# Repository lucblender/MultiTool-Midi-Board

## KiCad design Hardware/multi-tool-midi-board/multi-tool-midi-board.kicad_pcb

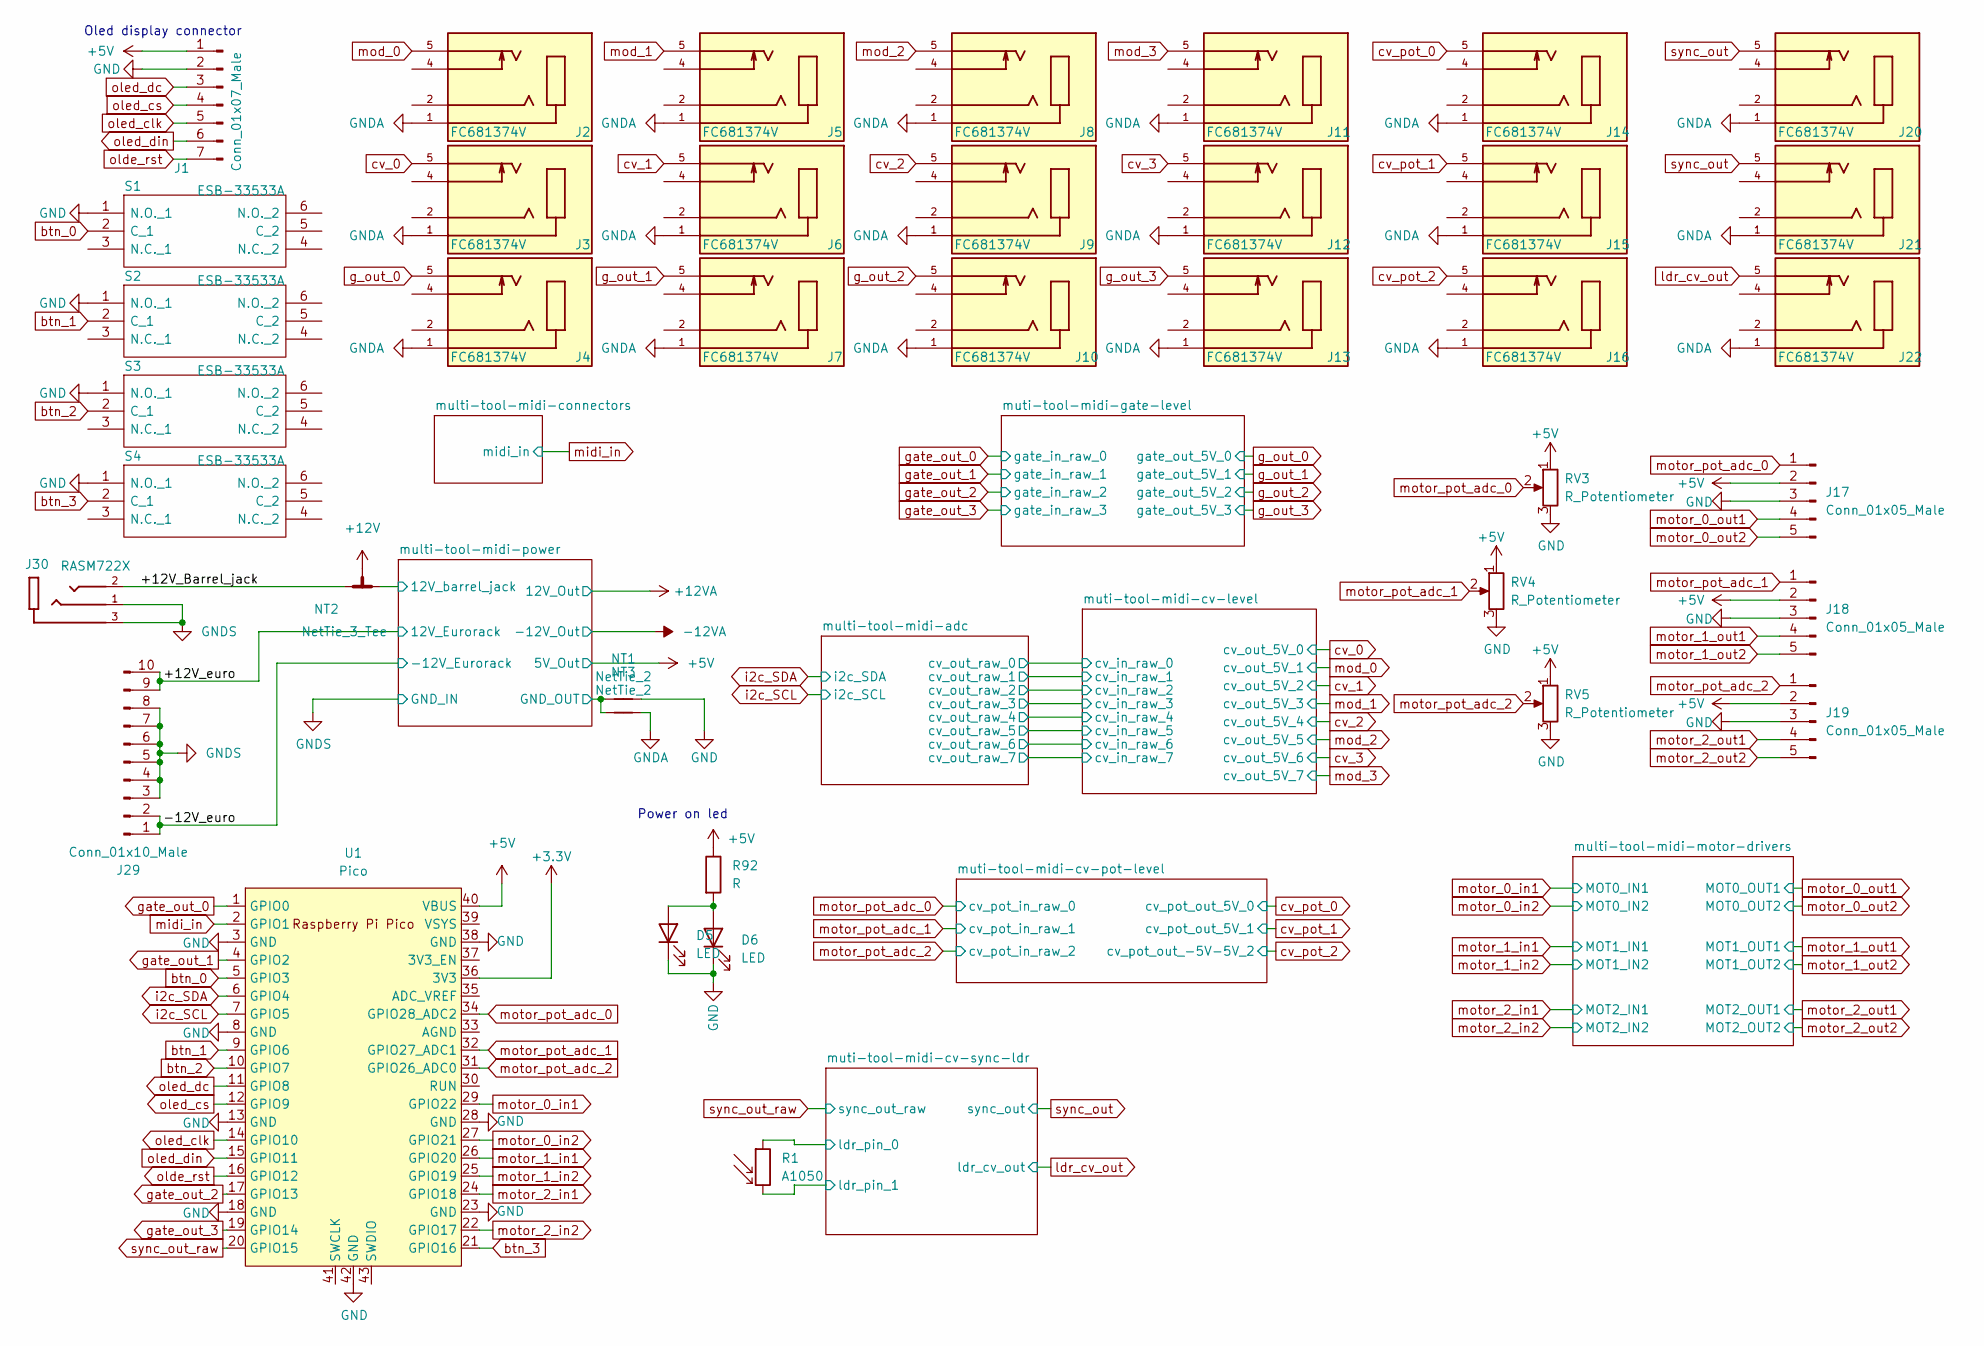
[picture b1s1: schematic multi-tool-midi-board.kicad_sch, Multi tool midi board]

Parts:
D5: LED; LED_D3.0mm
D6: LED; LED_0603_1608Metric
J1: Conn_01x07_Male; PinHeader_1x07_P2.54mm_Vertical
J2, J3, J4, J5, J6, J7, J8, J9, J10, J11, J12, J13, J14, J15, J16, J20, J21, J22: FC681374V; CLIFF_FC681374V
J17, J18, J19: Conn_01x05_Male; PinHeader_1x05_P2.54mm_Vertical
J29: Conn_01x10_Male; PinHeader_2x05_P2.54mm_Vertical
J30: RASM722X; SWITCHCRAFT_RASM722X; PARTREV A
NT1, NT3: NetTie_2; NetTie-2_SMD_Pad2.0mm
NT2: NetTie_3_Tee; NetTie-3_SMD_Pad2.0mm
R1: A1050; R_LDR_D6.4mm_P3.4mm_Vertical
R92: R; R_0805_2012Metric
RV3, RV4, RV5: R_Potentiometer; Potentiometer_Alpha_RD901F-40-00D_Single_Vertical
S1, S2, S3, S4: ESB-33533A; ESB33533A; Mouser Part Number 667-ESB-33533A
U1: Pico; RPi_Pico_SMD_TH

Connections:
+3V3: U1.36 (3V3); also elsewhere on the board
+5V: J1.1, J17.2, J18.2, J19.2, R92.1, RV3.1, RV4.1, RV5.1, U1.40 (VBUS); also elsewhere on the board
+12V: NT2.3; also elsewhere on the board
+12VA: R1.1; also elsewhere on the board
/+12V_Barrel_jack: J30.2, NT2.2
/+12V_euro: J29.9, J29.10; also elsewhere on the board
/-12V_euro: J29.1, J29.2; also elsewhere on the board
/multi-tool-midi-power/12V_barrel_jack: NT2.1; also elsewhere on the board
/muti-tool-midi-cv-sync-ldr/ldr_pin_1: R1.2; also elsewhere on the board
GND: D5.1 (K), D6.1 (K), J1.2, J17.3, J18.3, J19.3, NT1.2, RV3.3, RV4.3, RV5.3, S1.1 (N.O._1), S2.1 (N.O._1), S3.1 (N.O._1), S4.1 (N.O._1), U1.3 (GND), U1.8 (GND), U1.13 (GND), U1.18 (GND), U1.23 (GND), U1.28 (GND), U1.38 (GND), U1.42 (GND); also elsewhere on the board
GNDA: J2.1, J3.1, J4.1, J5.1, J6.1, J7.1, J8.1, J9.1, J10.1, J11.1, J12.1, J13.1, J14.1, J15.1, J16.1, J20.1, J21.1, J22.1, NT3.2; also elsewhere on the board
GNDS: J29.3, J29.4, J29.5, J29.6, J29.7, J29.8, J30.1, J30.3, NT1.1, NT3.1; also elsewhere on the board
unnamed: D5.2 (A), D6.2 (A), R92.2
btn_0: S1.2 (C_1), U1.5 (GPIO3)
btn_1: S2.2 (C_1), U1.9 (GPIO6)
btn_2: S3.2 (C_1), U1.10 (GPIO7)
btn_3: S4.2 (C_1), U1.21 (GPIO16)
cv_0: J3.5; also elsewhere on the board
cv_1: J6.5; also elsewhere on the board
cv_2: J9.5; also elsewhere on the board
cv_3: J12.5; also elsewhere on the board
cv_pot_0: J14.5; also elsewhere on the board
cv_pot_1: J15.5; also elsewhere on the board
cv_pot_2: J16.5; also elsewhere on the board
g_out_0: J4.5; also elsewhere on the board
g_out_1: J7.5; also elsewhere on the board
g_out_2: J10.5; also elsewhere on the board
g_out_3: J13.5; also elsewhere on the board
gate_out_0: U1.1 (GPIO0); also elsewhere on the board
gate_out_1: U1.4 (GPIO2); also elsewhere on the board
gate_out_2: U1.17 (GPIO13); also elsewhere on the board
gate_out_3: U1.19 (GPIO14); also elsewhere on the board
i2c_SCL: U1.7 (GPIO5); also elsewhere on the board
i2c_SDA: U1.6 (GPIO4); also elsewhere on the board
ldr_cv_out: J22.5; also elsewhere on the board
midi_in: U1.2 (GPIO1); also elsewhere on the board
mod_0: J2.5; also elsewhere on the board
mod_1: J5.5; also elsewhere on the board
mod_2: J8.5; also elsewhere on the board
mod_3: J11.5; also elsewhere on the board
motor_0_in1: U1.29 (GPIO22); also elsewhere on the board
motor_0_in2: U1.27 (GPIO21); also elsewhere on the board
motor_0_out1: J17.4; also elsewhere on the board
motor_0_out2: J17.5; also elsewhere on the board
motor_1_in1: U1.26 (GPIO20); also elsewhere on the board
motor_1_in2: U1.25 (GPIO19); also elsewhere on the board
motor_1_out1: J18.4; also elsewhere on the board
motor_1_out2: J18.5; also elsewhere on the board
motor_2_in1: U1.24 (GPIO18); also elsewhere on the board
motor_2_in2: U1.22 (GPIO17); also elsewhere on the board
motor_2_out1: J19.4; also elsewhere on the board
motor_2_out2: J19.5; also elsewhere on the board
motor_pot_adc_0: J17.1, RV3.2, U1.34 (GPIO28_ADC2); also elsewhere on the board
motor_pot_adc_1: J18.1, RV4.2, U1.32 (GPIO27_ADC1); also elsewhere on the board
motor_pot_adc_2: J19.1, RV5.2, U1.31 (GPIO26_ADC0); also elsewhere on the board
olde_rst: J1.7, U1.16 (GPIO12)
oled_clk: J1.5, U1.14 (GPIO10)
oled_cs: J1.4, U1.12 (GPIO9)
oled_dc: J1.3, U1.11 (GPIO8)
oled_din: J1.6, U1.15 (GPIO11)
sync_out: J20.5, J21.5; also elsewhere on the board
sync_out_raw: U1.20 (GPIO15); also elsewhere on the board

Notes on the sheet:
Power on led
Oled display connector

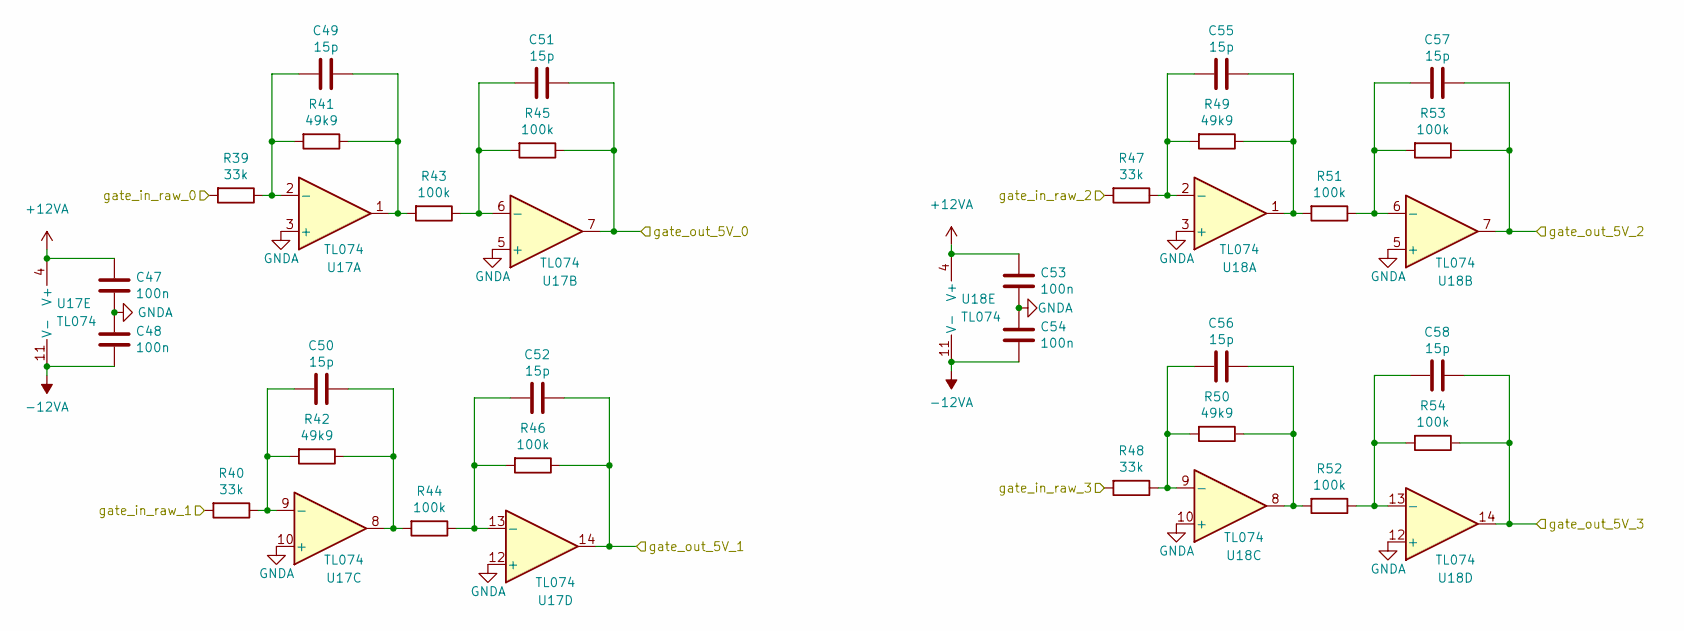
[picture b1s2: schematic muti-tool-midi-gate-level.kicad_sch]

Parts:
C47, C48, C53, C54: 100n; C_0603_1608Metric; LCSC C14663
C49, C50, C51, C52, C55, C56, C57, C58: 15p; C_0603_1608Metric; LCSC C14663
R39, R40, R47, R48: 33k; R_0603_1608Metric; LCSC C25804
R41, R42, R49, R50: 49k9; R_0603_1608Metric; LCSC C25804
R43, R44, R45, R46, R51, R52, R53, R54: 100k; R_0603_1608Metric; LCSC C25804
U17, U18: TL074; SOP50P326X110-14N

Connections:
+12VA: C47.1, C53.1, U17.4 (V+), U18.4 (V+); also elsewhere on the board
-12VA: C48.2, C54.2, U17.11 (V-), U18.11 (V-); also elsewhere on the board
GNDA: C47.2, C48.1, C53.2, C54.1, U17.3 (+), U17.5 (+), U17.10 (+), U17.12 (+), U18.3 (+), U18.5 (+), U18.10 (+), U18.12 (+); also elsewhere on the board
unnamed: C49.1, R39.1, R41.2, U17.2 (-)
unnamed: C49.2, R41.1, R43.2, U17.1
unnamed: C50.1, R40.1, R42.2, U17.9 (-)
unnamed: C50.2, R42.1, R44.2, U17.8
unnamed: C51.1, R43.1, R45.2, U17.6 (-)
unnamed: C52.1, R44.1, R46.2, U17.13 (-)
unnamed: C55.1, R47.1, R49.2, U18.2 (-)
unnamed: C55.2, R49.1, R51.2, U18.1
unnamed: C56.1, R48.1, R50.2, U18.9 (-)
unnamed: C56.2, R50.1, R52.2, U18.8
unnamed: C57.1, R51.1, R53.2, U18.6 (-)
unnamed: C58.1, R52.1, R54.2, U18.13 (-)
g_out_0: C51.2, R45.1, U17.7; also elsewhere on the board
g_out_1: C52.2, R46.1, U17.14; also elsewhere on the board
g_out_2: C57.2, R53.1, U18.7; also elsewhere on the board
g_out_3: C58.2, R54.1, U18.14; also elsewhere on the board
gate_out_0: R39.2; also elsewhere on the board
gate_out_1: R40.2; also elsewhere on the board
gate_out_2: R47.2; also elsewhere on the board
gate_out_3: R48.2; also elsewhere on the board

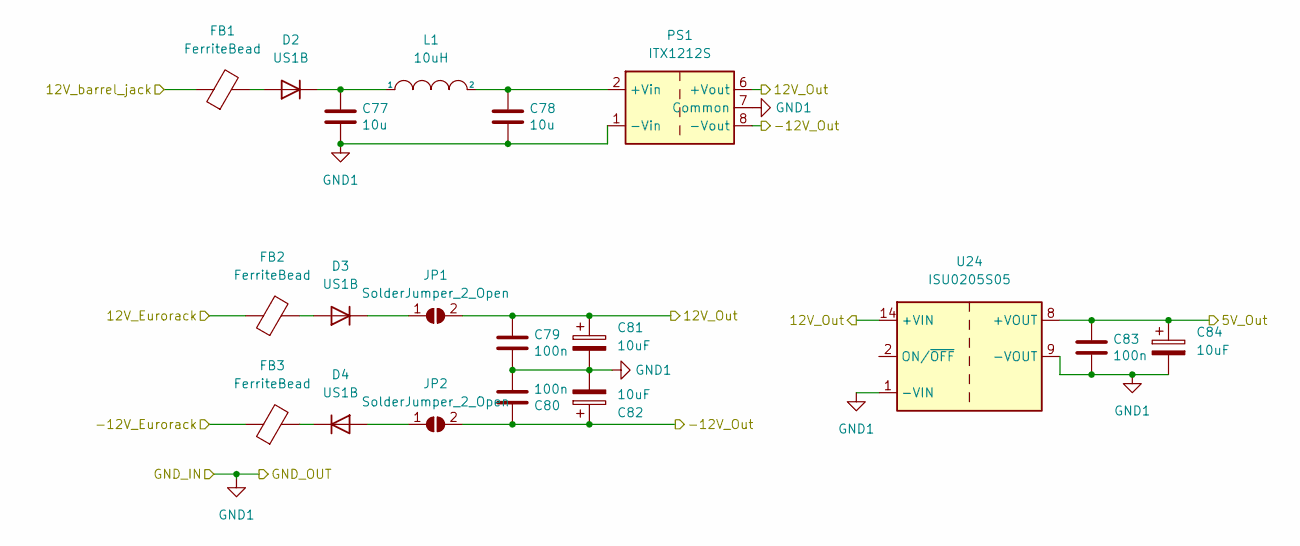
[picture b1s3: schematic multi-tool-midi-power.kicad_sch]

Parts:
C77, C78: 10u; C_0603_1608Metric; LCSC C14663
C79, C80, C83: 100n; C_0603_1608Metric; LCSC C14663
C81, C82, C84: 10uF; CP_Elec_6.3x5.9
D2, D3, D4: US1B; D_SMA
FB1, FB2, FB3: FerriteBead; L_0805_2012Metric
JP1, JP2: SolderJumper_2_Open; SolderJumper-2_P1.3mm_Open_TrianglePad1.0x1.5mm
L1: 10uH; L_0805_2012Metric
PS1: ITX1212S; Converter_DCDC_XP_POWER-ITxxxxxS_THT
U24: ISU0205S05; Converter_DCDC_XP_POWER-ISU02_SMD

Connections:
+5V: C83.1, C84.1, U24.8 (+VOUT); also elsewhere on the board
+12VA: C79.1, C81.1, JP1.2 (B), PS1.6 (+Vout), U24.14 (+VIN); also elsewhere on the board
-12VA: C80.1, C82.1, JP2.2 (B), PS1.8 (-Vout); also elsewhere on the board
/+12V_euro: FB2.1; also elsewhere on the board
/-12V_euro: FB3.1; also elsewhere on the board
/multi-tool-midi-power/12V_barrel_jack: FB1.1; also elsewhere on the board
GNDS: C77.2, C78.2, C79.2, C80.2, C81.2, C82.2, C83.2, C84.2, PS1.1 (-Vin), PS1.7 (Common), U24.1 (-VIN), U24.9 (-VOUT); also elsewhere on the board
unnamed: C77.1, D2.1 (K), L1.1
unnamed: C78.1, L1.2, PS1.2 (+Vin)
unnamed: D2.2 (A), FB1.2
unnamed: D3.1 (K), JP1.1 (A)
unnamed: D3.2 (A), FB2.2
unnamed: D4.1 (K), FB3.2
unnamed: D4.2 (A), JP2.1 (A)

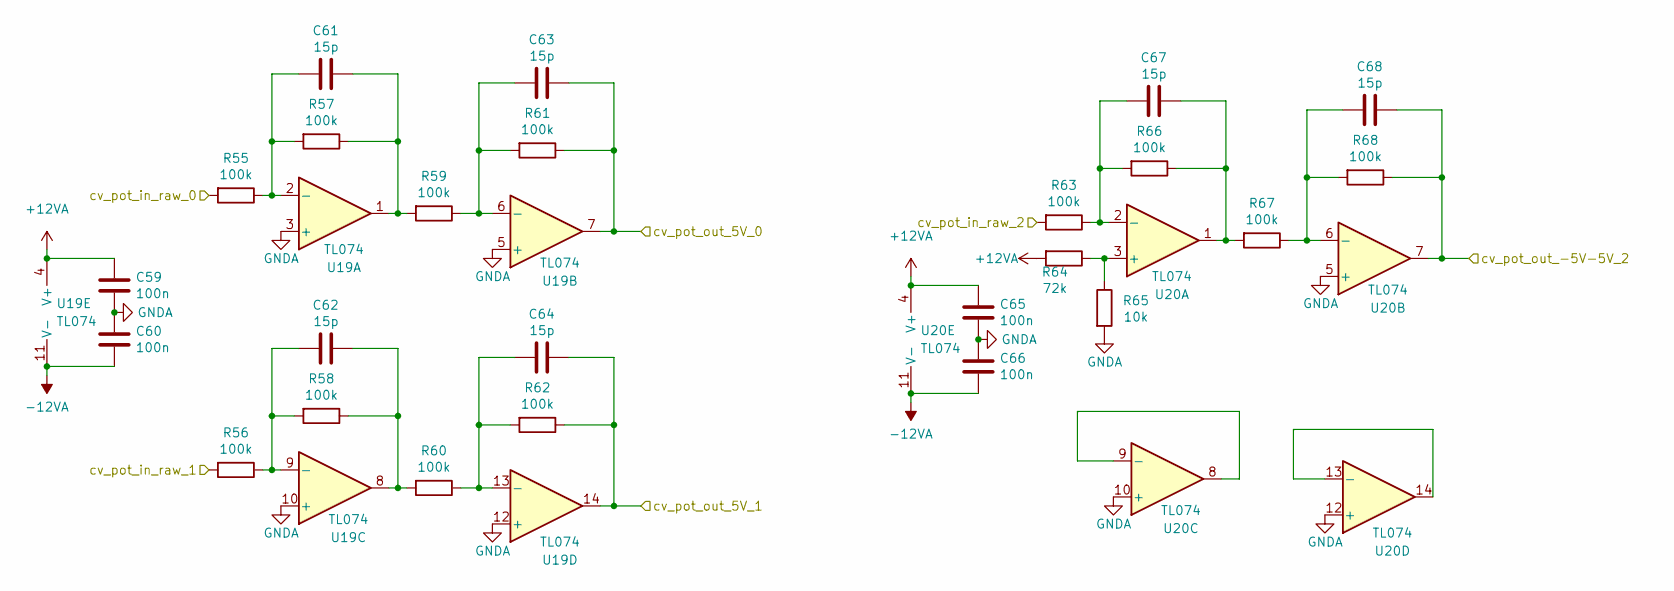
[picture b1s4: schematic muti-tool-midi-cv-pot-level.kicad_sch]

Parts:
C59, C60, C65, C66: 100n; C_0603_1608Metric; LCSC C14663
C61, C62, C63, C64, C67, C68: 15p; C_0603_1608Metric; LCSC C14663
R55, R56, R57, R58, R59, R60, R61, R62, R63, R66, R67, R68: 100k; R_0603_1608Metric; LCSC C25804
R64: 72k; R_0603_1608Metric; LCSC C25804
R65: 10k; R_0603_1608Metric; LCSC C25804
U19, U20: TL074; SOP50P326X110-14N

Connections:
+12VA: C59.1, C65.1, R64.2, U19.4 (V+), U20.4 (V+); also elsewhere on the board
-12VA: C60.2, C66.2, U19.11 (V-), U20.11 (V-); also elsewhere on the board
GNDA: C59.2, C60.1, C65.2, C66.1, R65.2, U19.3 (+), U19.5 (+), U19.10 (+), U19.12 (+), U20.5 (+), U20.10 (+), U20.12 (+); also elsewhere on the board
unnamed: C61.1, R55.1, R57.2, U19.2 (-)
unnamed: C61.2, R57.1, R59.2, U19.1
unnamed: C62.1, R56.1, R58.2, U19.9 (-)
unnamed: C62.2, R58.1, R60.2, U19.8
unnamed: C63.1, R59.1, R61.2, U19.6 (-)
unnamed: C64.1, R60.1, R62.2, U19.13 (-)
unnamed: C67.1, R63.1, R66.2, U20.2 (-)
unnamed: C67.2, R66.1, R67.2, U20.1
unnamed: C68.1, R67.1, R68.2, U20.6 (-)
unnamed: R64.1, R65.1, U20.3 (+)
unnamed: U20.8, U20.9 (-)
unnamed: U20.13 (-), U20.14
cv_pot_0: C63.2, R61.1, U19.7; also elsewhere on the board
cv_pot_1: C64.2, R62.1, U19.14; also elsewhere on the board
cv_pot_2: C68.2, R68.1, U20.7; also elsewhere on the board
motor_pot_adc_0: R55.2; also elsewhere on the board
motor_pot_adc_1: R56.2; also elsewhere on the board
motor_pot_adc_2: R63.2; also elsewhere on the board

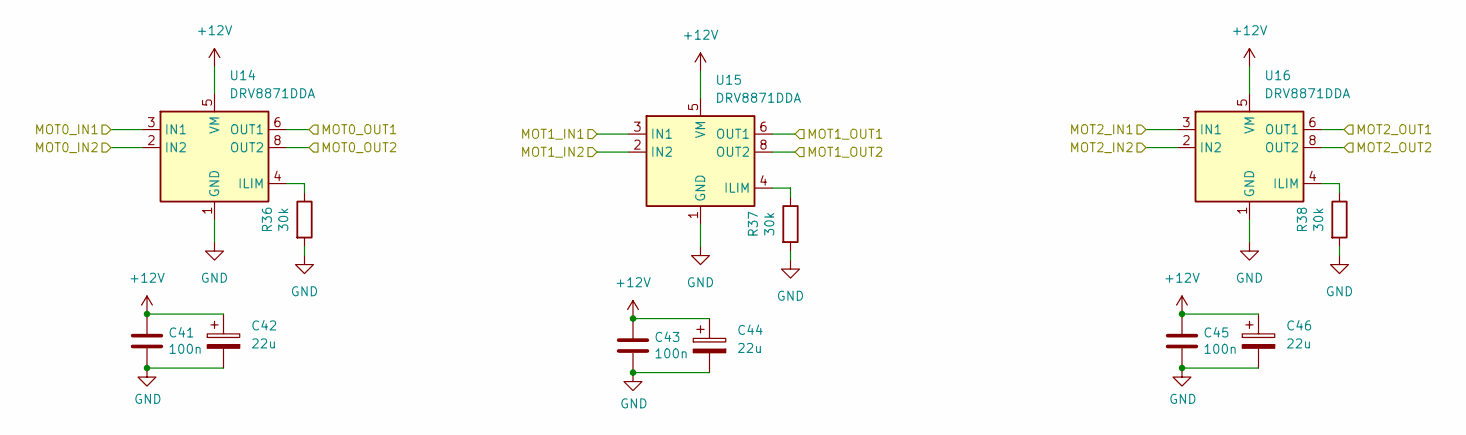
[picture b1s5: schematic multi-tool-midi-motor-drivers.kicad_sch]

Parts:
C41, C43, C45: 100n; C_0603_1608Metric; LCSC C14663
C42, C44, C46: 22u; CP_Elec_6.3x5.9
R36, R37, R38: 30k; R_0603_1608Metric; LCSC C25804
U14, U15, U16: DRV8871DDA; Texas_HTSOP-8-1EP_3.9x4.9mm_P1.27mm_EP2.95x4.9mm_Mask2.4x3.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

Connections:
+12V: C41.1, C42.1, C43.1, C44.1, C45.1, C46.1, U14.5 (VM), U15.5 (VM), U16.5 (VM); also elsewhere on the board
GND: C41.2, C42.2, C43.2, C44.2, C45.2, C46.2, R36.2, R37.2, R38.2, U14.1 (GND), U14.7 (GND), U14.9 (GND), U15.1 (GND), U15.7 (GND), U15.9 (GND), U16.1 (GND), U16.7 (GND), U16.9 (GND); also elsewhere on the board
unnamed: R36.1, U14.4 (ILIM)
unnamed: R37.1, U15.4 (ILIM)
unnamed: R38.1, U16.4 (ILIM)
motor_0_in1: U14.3 (IN1); also elsewhere on the board
motor_0_in2: U14.2 (IN2); also elsewhere on the board
motor_0_out1: U14.6 (OUT1); also elsewhere on the board
motor_0_out2: U14.8 (OUT2); also elsewhere on the board
motor_1_in1: U15.3 (IN1); also elsewhere on the board
motor_1_in2: U15.2 (IN2); also elsewhere on the board
motor_1_out1: U15.6 (OUT1); also elsewhere on the board
motor_1_out2: U15.8 (OUT2); also elsewhere on the board
motor_2_in1: U16.3 (IN1); also elsewhere on the board
motor_2_in2: U16.2 (IN2); also elsewhere on the board
motor_2_out1: U16.6 (OUT1); also elsewhere on the board
motor_2_out2: U16.8 (OUT2); also elsewhere on the board

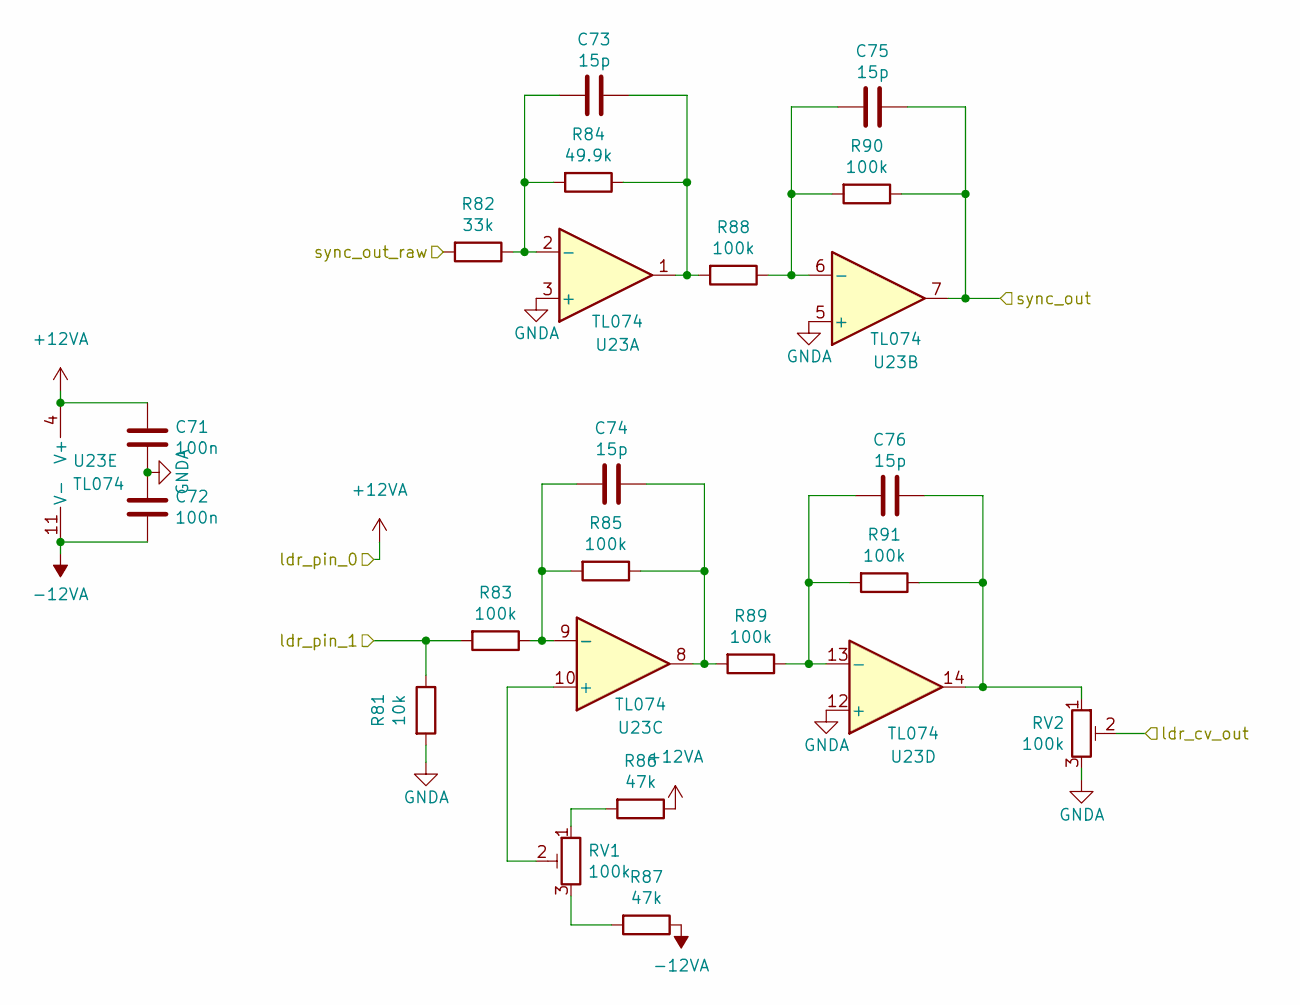
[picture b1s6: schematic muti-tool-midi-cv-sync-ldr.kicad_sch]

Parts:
C71, C72: 100n; C_0603_1608Metric; LCSC C14663
C73, C74, C75, C76: 15p; C_0603_1608Metric; LCSC C14663
R81: 10k; R_0603_1608Metric; LCSC C25804
R82: 33k; R_0603_1608Metric; LCSC C25804
R83, R85, R88, R89, R90, R91: 100k; R_0603_1608Metric; LCSC C25804
R84: 49.9k; R_0603_1608Metric; LCSC C25804
R86, R87: 47k; R_0603_1608Metric; LCSC C25804
RV1, RV2: 100k; Potentiometer_Vishay_TS53YL_Vertical
U23: TL074; SOP50P326X110-14N

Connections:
+12VA: C71.1, R86.1, U23.4 (V+); also elsewhere on the board
-12VA: C72.2, R87.1, U23.11 (V-); also elsewhere on the board
/muti-tool-midi-cv-sync-ldr/ldr_pin_1: R81.1, R83.2; also elsewhere on the board
GNDA: C71.2, C72.1, R81.2, RV2.3, U23.3 (+), U23.5 (+), U23.12 (+); also elsewhere on the board
unnamed: C73.1, R82.1, R84.2, U23.2 (-)
unnamed: C73.2, R84.1, R88.2, U23.1
unnamed: C74.1, R83.1, R85.2, U23.9 (-)
unnamed: C74.2, R85.1, R89.2, U23.8
unnamed: C75.1, R88.1, R90.2, U23.6 (-)
unnamed: C76.1, R89.1, R91.2, U23.13 (-)
unnamed: C76.2, R91.1, RV2.1, U23.14
unnamed: R86.2, RV1.1
unnamed: R87.2, RV1.3
unnamed: RV1.2, U23.10 (+)
ldr_cv_out: RV2.2; also elsewhere on the board
sync_out: C75.2, R90.1, U23.7; also elsewhere on the board
sync_out_raw: R82.2; also elsewhere on the board

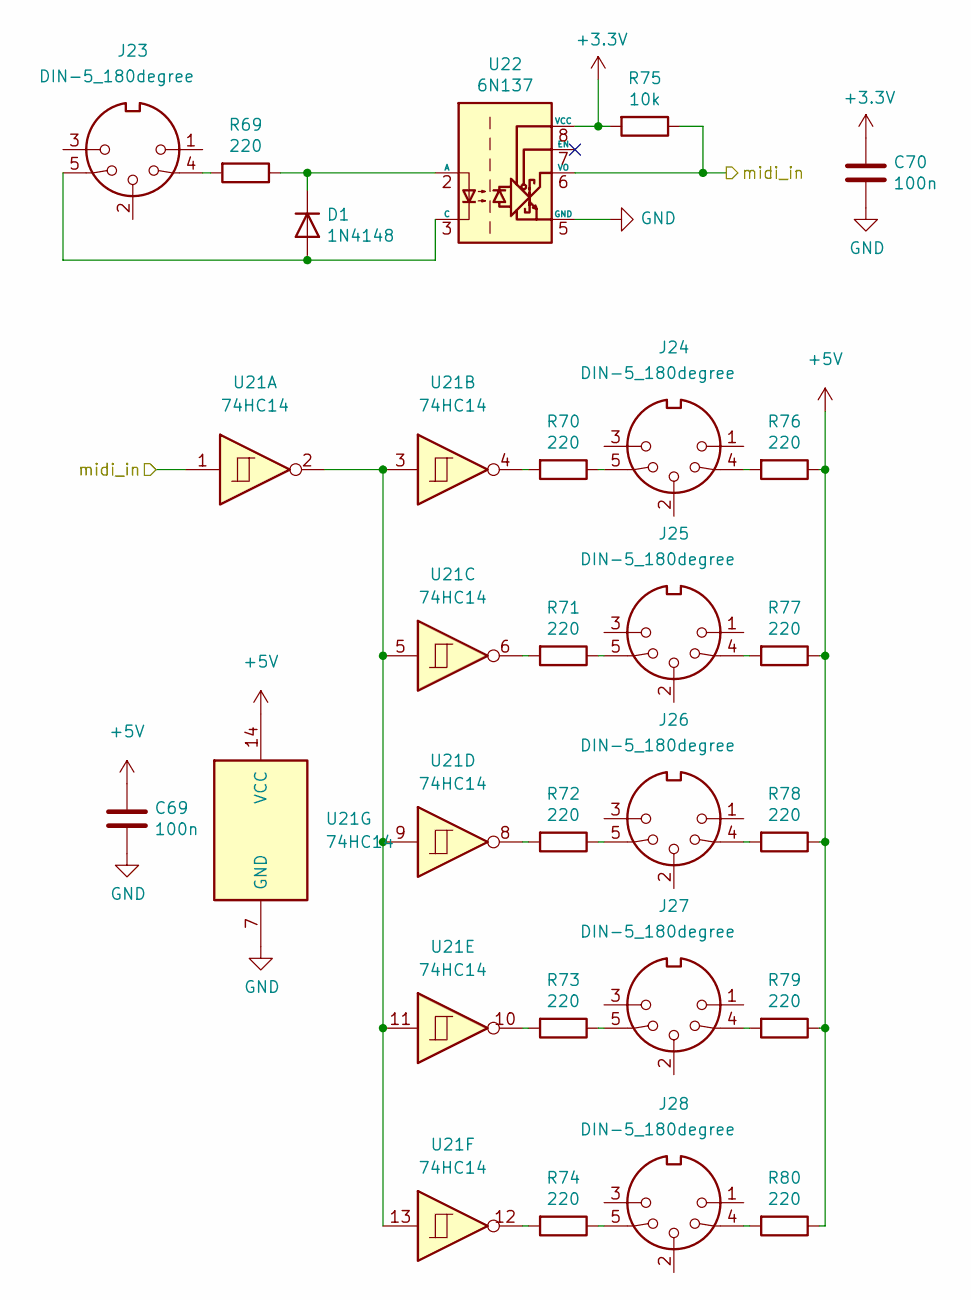
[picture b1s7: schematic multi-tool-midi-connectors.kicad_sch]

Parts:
C69, C70: 100n; C_0603_1608Metric; LCSC C14663
D1: 1N4148; D_SOD-123; LCSC C81598
J23, J24, J25, J26, J27, J28: DIN-5_180degree; CUI_SD-50BV
R69: 220; R_0603_1608Metric; LCSC C22962
R70, R71, R72, R73, R74, R76, R77, R78, R79, R80: 220; R_0603_1608Metric; LCSC C25804
R75: 10k; R_0603_1608Metric; LCSC C25804
U21: 74HC14; SOIC-14_3.9x8.7mm_P1.27mm
U22: 6N137; SMDIP-8_W9.53mm; LCSC C110020

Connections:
+3V3: C70.1, R75.2, U22.8 (VCC); also elsewhere on the board
+5V: C69.1, R76.1, R77.1, R78.1, R79.1, R80.1, U21.14 (VCC); also elsewhere on the board
GND: C69.2, C70.2, U21.7 (GND), U22.5 (GND); also elsewhere on the board
unnamed: D1.1 (K), R69.1, U22.2 (A)
unnamed: D1.2 (A), J23.5, U22.3 (C)
unnamed: J23.4, R69.2
unnamed: J24.4, R76.2
unnamed: J24.5, R70.1
unnamed: J25.4, R77.2
unnamed: J25.5, R71.1
unnamed: J26.4, R78.2
unnamed: J26.5, R72.1
unnamed: J27.4, R79.2
unnamed: J27.5, R73.1
unnamed: J28.4, R80.2
unnamed: J28.5, R74.1
unnamed: R70.2, U21.4
unnamed: R71.2, U21.6
unnamed: R72.2, U21.8
unnamed: R73.2, U21.10
unnamed: R74.2, U21.12
unnamed: U21.2, U21.3, U21.5, U21.9, U21.11, U21.13
midi_in: R75.1, U21.1, U22.6 (VO); also elsewhere on the board

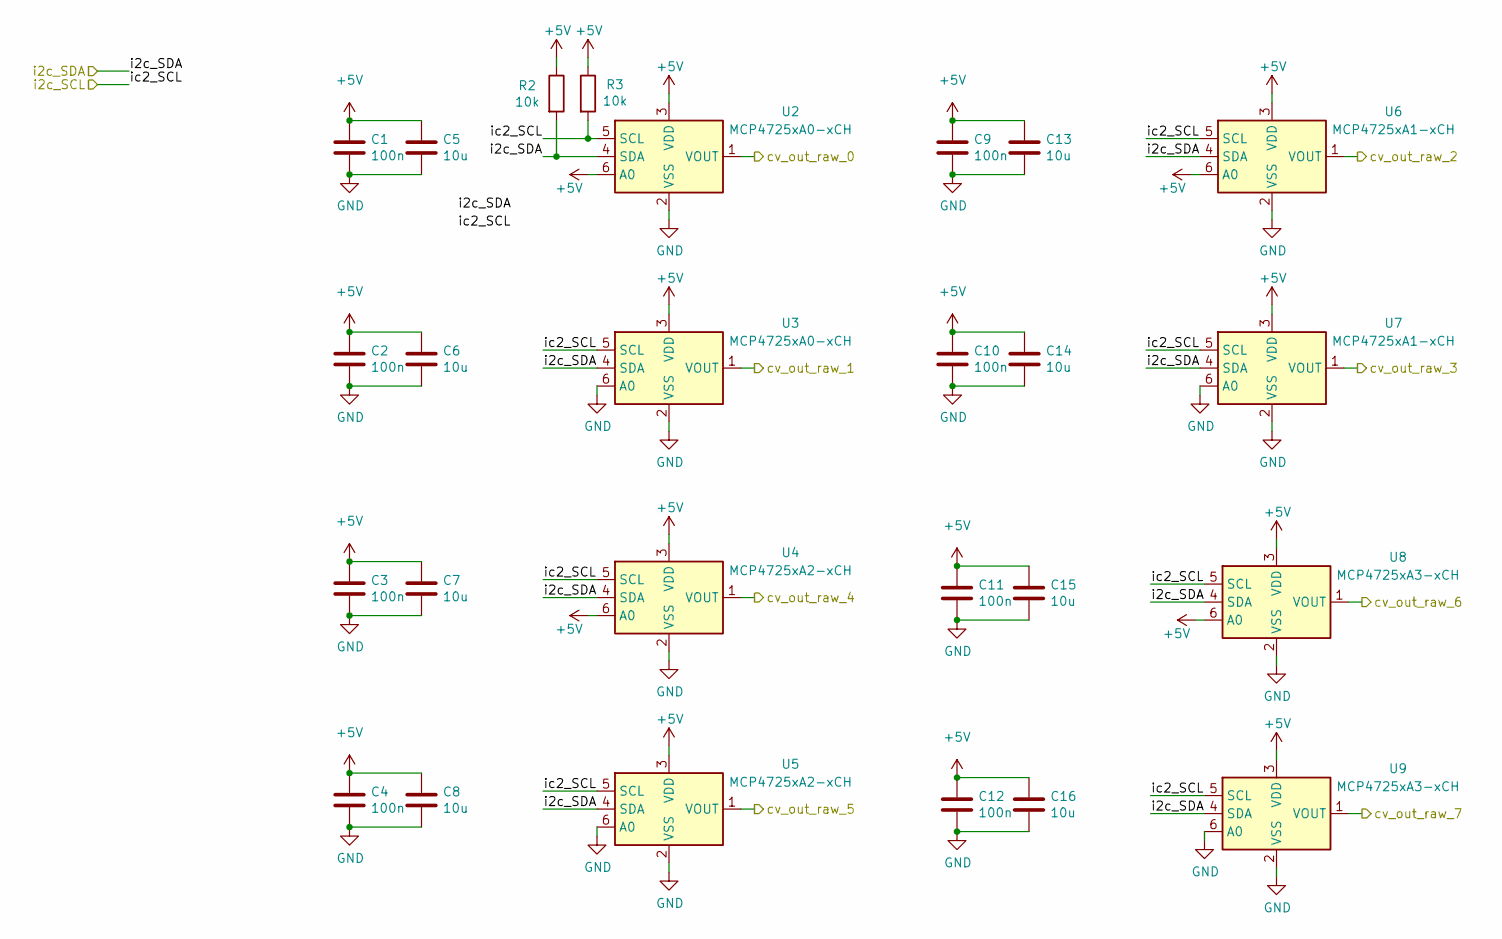
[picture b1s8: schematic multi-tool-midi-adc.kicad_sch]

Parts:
C1, C2, C3, C4, C9, C10, C11, C12: 100n; C_0603_1608Metric; LCSC C14663
C5, C6, C7, C8, C13, C14, C15, C16: 10u; C_0603_1608Metric; LCSC C14663
R2, R3: 10k; R_0603_1608Metric; LCSC C25804
U2, U3: MCP4725xA0-xCH; SOT-23-6
U4, U5: MCP4725xA2-xCH; SOT-23-6
U6, U7: MCP4725xA1-xCH; SOT-23-6
U8, U9: MCP4725xA3-xCH; SOT-23-6

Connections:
+5V: C1.1, C2.1, C3.1, C4.1, C5.1, C6.1, C7.1, C8.1, C9.1, C10.1, C11.1, C12.1, C13.1, C14.1, C15.1, C16.1, R2.1, R3.1, U2.3 (VDD), U2.6 (A0), U3.3 (VDD), U4.3 (VDD), U4.6 (A0), U5.3 (VDD), U6.3 (VDD), U6.6 (A0), U7.3 (VDD), U8.3 (VDD), U8.6 (A0), U9.3 (VDD); also elsewhere on the board
/multi-tool-midi-adc/cv_out_raw_0: U2.1 (VOUT); also elsewhere on the board
/multi-tool-midi-adc/cv_out_raw_1: U3.1 (VOUT); also elsewhere on the board
/multi-tool-midi-adc/cv_out_raw_2: U6.1 (VOUT); also elsewhere on the board
/multi-tool-midi-adc/cv_out_raw_3: U7.1 (VOUT); also elsewhere on the board
/multi-tool-midi-adc/cv_out_raw_4: U4.1 (VOUT); also elsewhere on the board
/multi-tool-midi-adc/cv_out_raw_5: U5.1 (VOUT); also elsewhere on the board
/multi-tool-midi-adc/cv_out_raw_6: U8.1 (VOUT); also elsewhere on the board
/multi-tool-midi-adc/cv_out_raw_7: U9.1 (VOUT); also elsewhere on the board
GND: C1.2, C2.2, C3.2, C4.2, C5.2, C6.2, C7.2, C8.2, C9.2, C10.2, C11.2, C12.2, C13.2, C14.2, C15.2, C16.2, U2.2 (VSS), U3.2 (VSS), U3.6 (A0), U4.2 (VSS), U5.2 (VSS), U5.6 (A0), U6.2 (VSS), U7.2 (VSS), U7.6 (A0), U8.2 (VSS), U9.2 (VSS), U9.6 (A0); also elsewhere on the board
i2c_SCL: R3.2, U2.5 (SCL), U3.5 (SCL), U4.5 (SCL), U5.5 (SCL), U6.5 (SCL), U7.5 (SCL), U8.5 (SCL), U9.5 (SCL); also elsewhere on the board
i2c_SDA: R2.2, U2.4 (SDA), U3.4 (SDA), U4.4 (SDA), U5.4 (SDA), U6.4 (SDA), U7.4 (SDA), U8.4 (SDA), U9.4 (SDA); also elsewhere on the board

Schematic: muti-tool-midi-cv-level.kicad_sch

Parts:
C17, C18, C19, C20, C29, C30, C31, C32: 100n; C_0603_1608Metric; LCSC C14663
C21, C22, C23, C24, C25, C26, C27, C28, C33, C34, C35, C36, C37, C38, C39, C40: 15p; C_0603_1608Metric; LCSC C14663
R4, R5, R6, R7, R20, R21, R22, R23: 25k; R_0603_1608Metric; LCSC C25804
R8, R9, R10, R11, R24, R25, R26, R27: 49k9; R_0603_1608Metric; LCSC C25804
R12, R13, R14, R15, R16, R17, R18, R19, R28, R29, R30, R31, R32, R33, R34, R35: 100k; R_0603_1608Metric; LCSC C25804
U10, U11, U12, U13: TL074; SOP50P326X110-14N

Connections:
+12VA: C17.1, C19.1, C29.1, C31.1, U10.4 (V+), U11.4 (V+), U12.4 (V+), U13.4 (V+); also elsewhere on the board
-12VA: C18.2, C20.2, C30.2, C32.2, U10.11 (V-), U11.11 (V-), U12.11 (V-), U13.11 (V-); also elsewhere on the board
/multi-tool-midi-adc/cv_out_raw_0: R4.2; also elsewhere on the board
/multi-tool-midi-adc/cv_out_raw_1: R6.2; also elsewhere on the board
/multi-tool-midi-adc/cv_out_raw_2: R20.2; also elsewhere on the board
/multi-tool-midi-adc/cv_out_raw_3: R21.2; also elsewhere on the board
/multi-tool-midi-adc/cv_out_raw_4: R5.2; also elsewhere on the board
/multi-tool-midi-adc/cv_out_raw_5: R7.2; also elsewhere on the board
/multi-tool-midi-adc/cv_out_raw_6: R22.2; also elsewhere on the board
/multi-tool-midi-adc/cv_out_raw_7: R23.2; also elsewhere on the board
GNDA: C17.2, C18.1, C19.2, C20.1, C29.2, C30.1, C31.2, C32.1, U10.3 (+), U10.5 (+), U10.10 (+), U10.12 (+), U11.3 (+), U11.5 (+), U11.10 (+), U11.12 (+), U12.3 (+), U12.5 (+), U12.10 (+), U12.12 (+), U13.3 (+), U13.5 (+), U13.10 (+), U13.12 (+); also elsewhere on the board
unnamed: C21.1, R4.1, R8.2, U10.2 (-)
unnamed: C21.2, R8.1, R12.2, U10.1
unnamed: C22.1, R5.1, R9.2, U11.2 (-)
unnamed: C22.2, R9.1, R13.2, U11.1
unnamed: C23.1, R6.1, R10.2, U10.9 (-)
unnamed: C23.2, R10.1, R14.2, U10.8
unnamed: C24.1, R7.1, R11.2, U11.9 (-)
unnamed: C24.2, R11.1, R15.2, U11.8
unnamed: C25.1, R12.1, R16.2, U10.6 (-)
unnamed: C26.1, R13.1, R17.2, U11.6 (-)
unnamed: C27.1, R14.1, R18.2, U10.13 (-)
unnamed: C28.1, R15.1, R19.2, U11.13 (-)
unnamed: C33.1, R20.1, R24.2, U12.2 (-)
unnamed: C33.2, R24.1, R28.2, U12.1
unnamed: C34.1, R21.1, R25.2, U12.9 (-)
unnamed: C34.2, R25.1, R29.2, U12.8
unnamed: C35.1, R22.1, R26.2, U13.2 (-)
unnamed: C35.2, R26.1, R30.2, U13.1
unnamed: C36.1, R23.1, R27.2, U13.9 (-)
unnamed: C36.2, R27.1, R31.2, U13.8
unnamed: C37.1, R28.1, R32.2, U12.6 (-)
unnamed: C38.1, R29.1, R33.2, U12.13 (-)
unnamed: C39.1, R30.1, R34.2, U13.6 (-)
unnamed: C40.1, R31.1, R35.2, U13.13 (-)
cv_0: C25.2, R16.1, U10.7; also elsewhere on the board
cv_1: C37.2, R32.1, U12.7; also elsewhere on the board
cv_2: C26.2, R17.1, U11.7; also elsewhere on the board
cv_3: C39.2, R34.1, U13.7; also elsewhere on the board
mod_0: C27.2, R18.1, U10.14; also elsewhere on the board
mod_1: C38.2, R33.1, U12.14; also elsewhere on the board
mod_2: C28.2, R19.1, U11.14; also elsewhere on the board
mod_3: C40.2, R35.1, U13.14; also elsewhere on the board

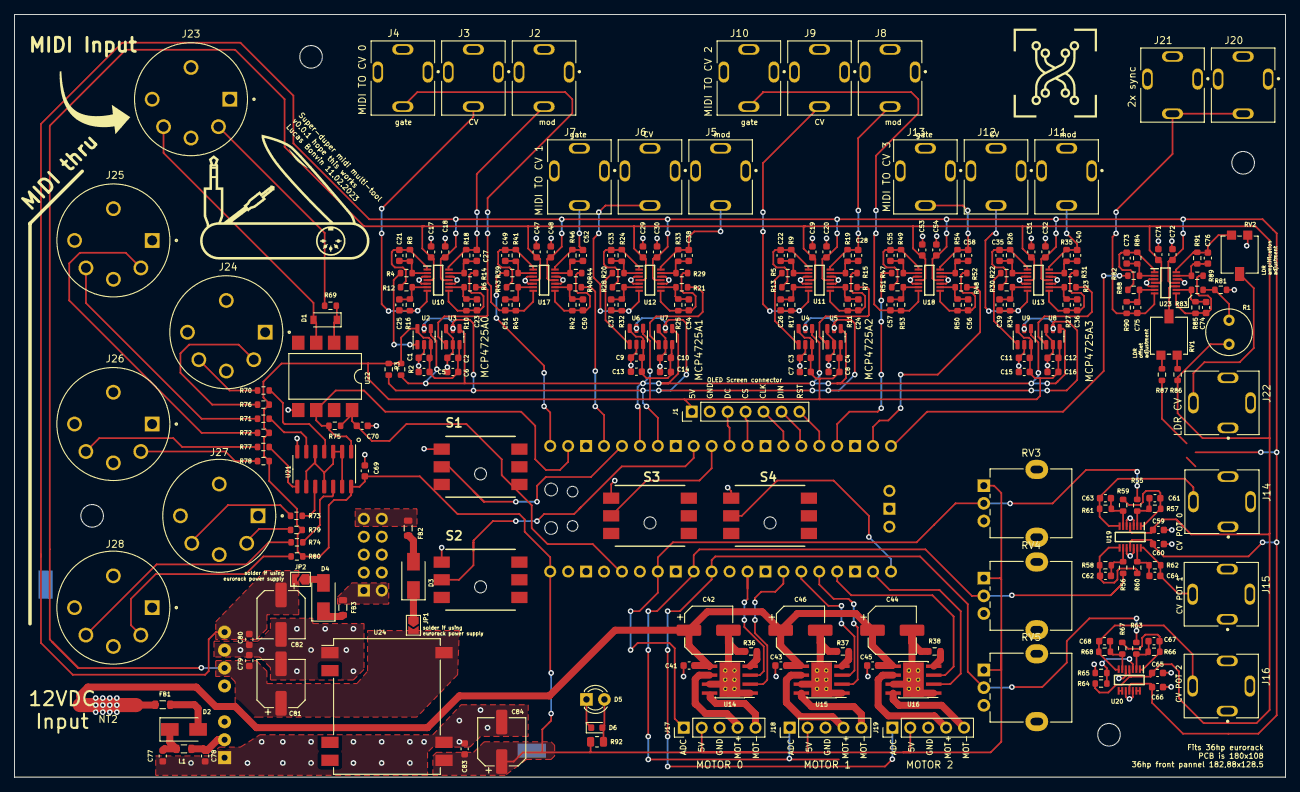
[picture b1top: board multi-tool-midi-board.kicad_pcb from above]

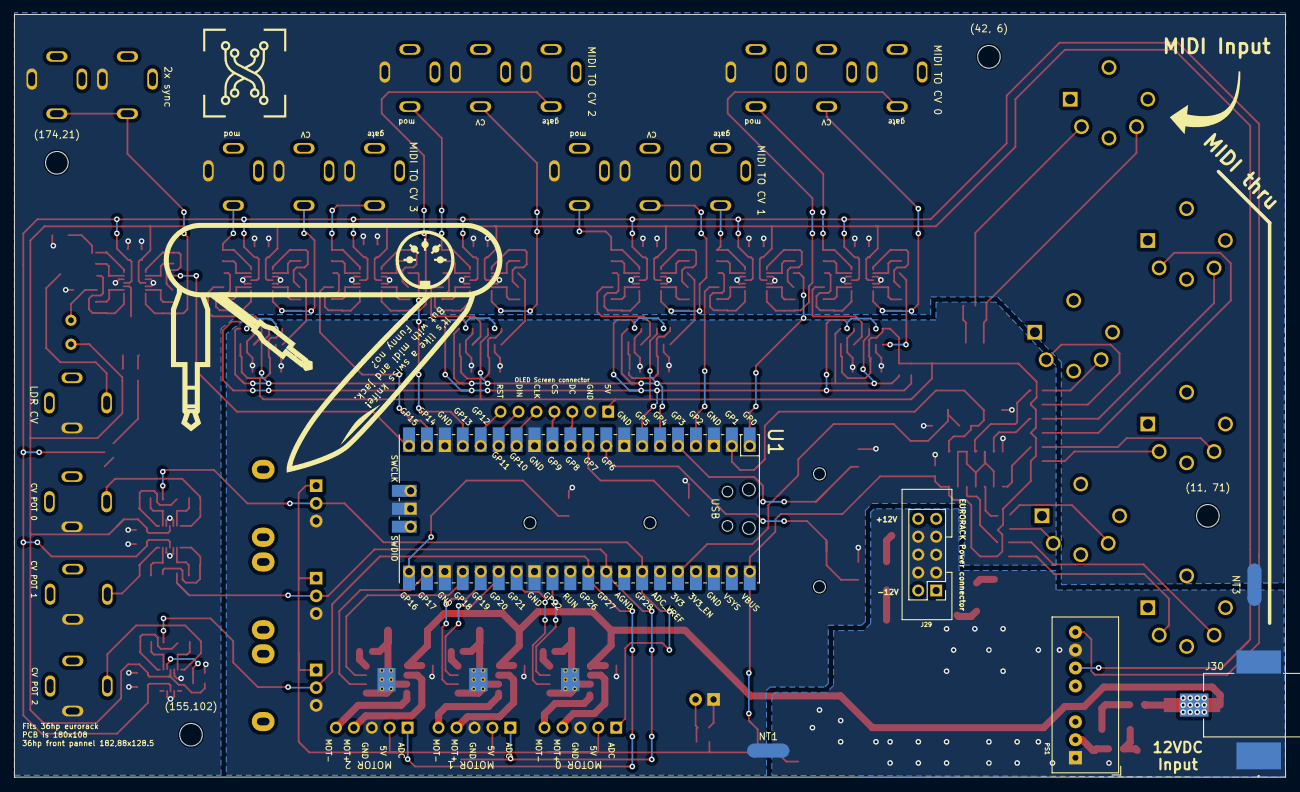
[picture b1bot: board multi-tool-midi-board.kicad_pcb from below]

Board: 2 copper layers, 180.0 x 108.0 mm, 255 parts (6 on the bottom side), 158 nets.

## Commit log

2023-04-30 add gitignore
2023-04-30 first commit of kicad projects
2023-04-30 commit of test code
2023-04-30 removed zip from git
2023-05-01 started midi to cv and screen
2023-05-02 add thread for midi and nice screensaver
2023-05-03 implemented menu navigation
2023-05-03 menu implementation on main
2023-05-06 add midi clock with subdivision and polarity
2023-05-06 change visualisation of -5 5V pot
2023-05-18 add data saving, velocity out instead of mod, debug screen at boot
2023-05-18 add usb detection
2023-05-19 add motorized potentiometer presets
